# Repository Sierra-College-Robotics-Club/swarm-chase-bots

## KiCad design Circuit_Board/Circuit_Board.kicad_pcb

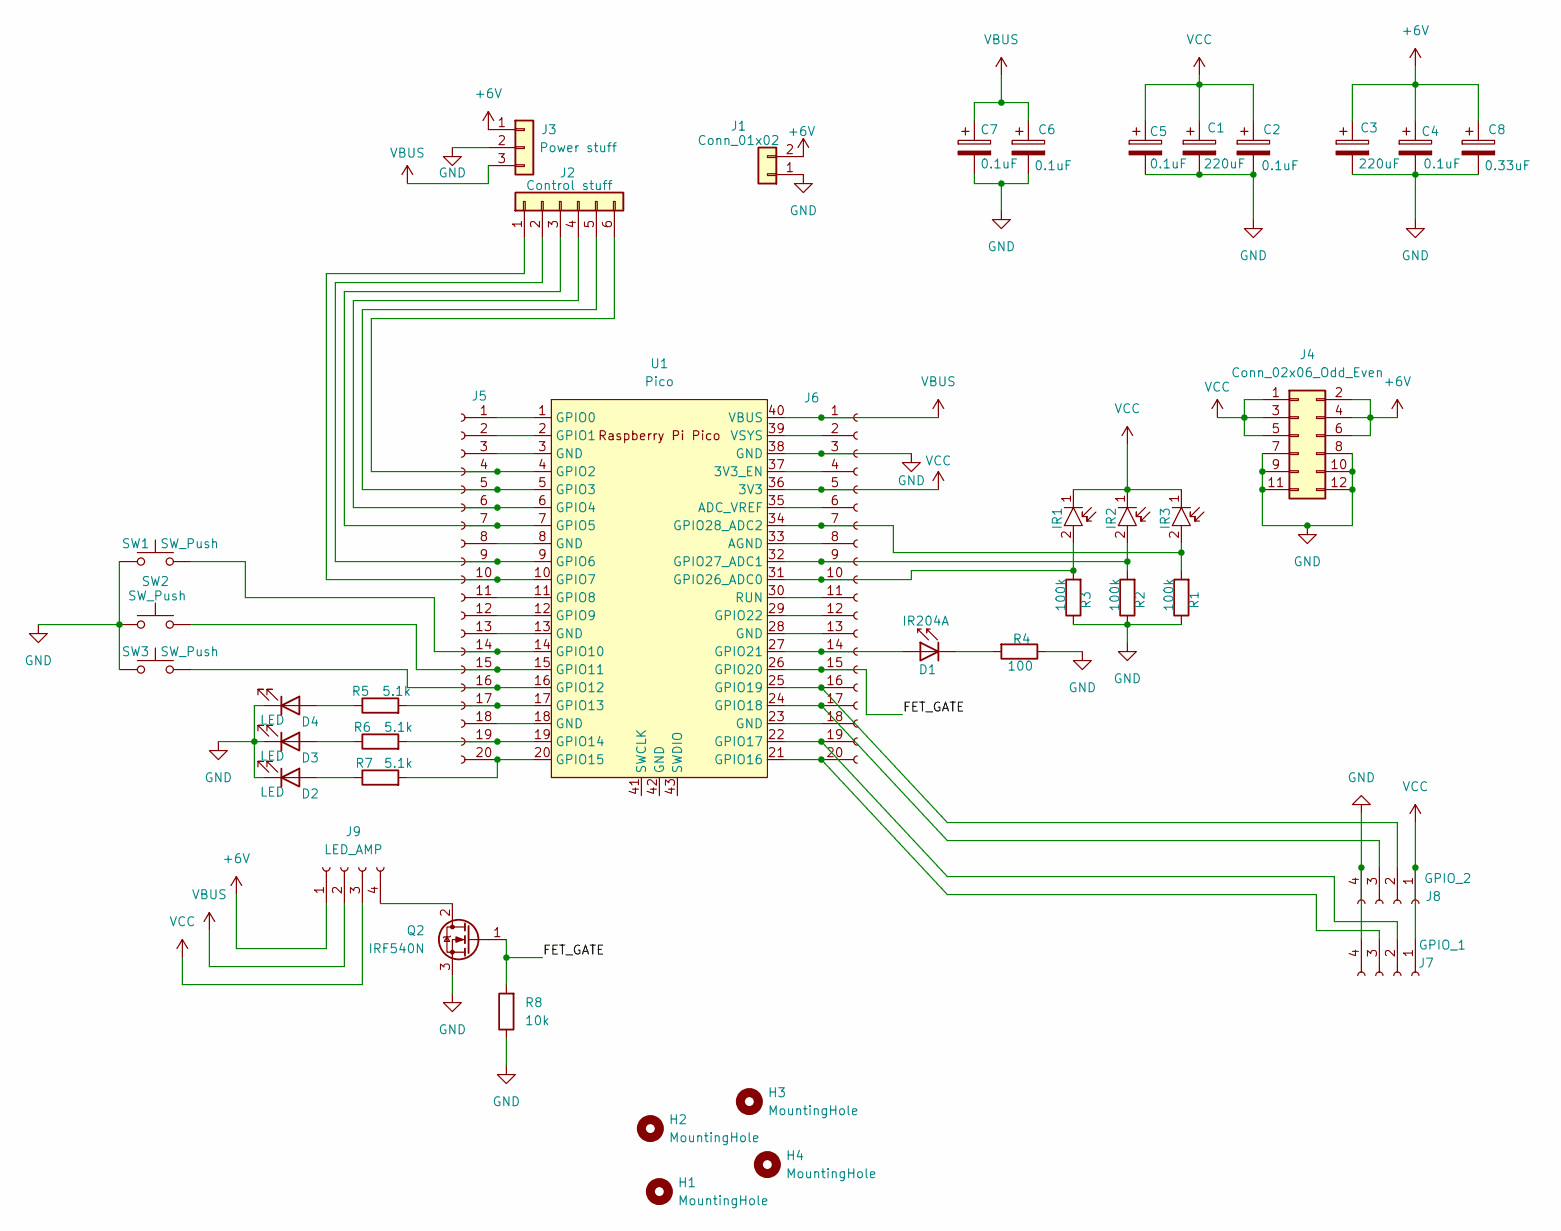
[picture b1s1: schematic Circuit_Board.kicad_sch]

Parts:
C1, C3: 220uF; CP_Radial_D10.0mm_P5.00mm
C2, C4, C5, C6, C7: 0.1uF; C_0805_2012Metric_Pad1.18x1.45mm_HandSolder
C8: 0.33uF; C_0805_2012Metric_Pad1.18x1.45mm_HandSolder
D1: IR204A; LED_D3.0mm_IRBlack
D2, D3, D4: LED; LED_0603_1608Metric_Pad1.05x0.95mm_HandSolder
H1, H2, H3, H4: MountingHole; MountingHole_3.2mm_M3
IR1, IR2, IR3: LED_D3.0mm
J1: Conn_01x02; AMASS_XT60-M_1x02_P7.20mm_Vertical
J2: Control stuff; JST_XH_B6B-XH-A_1x06_P2.50mm_Vertical
J3: Power stuff; JST_XH_B3B-XH-A_1x03_P2.50mm_Vertical
J4: Conn_02x06_Odd_Even; JST_PHD_B12B-PHDSS_2x06_P2.00mm_Vertical
J5, J6: Conn_01x20_Socket; PinSocket_1x20_P2.54mm_Vertical
J7: GPIO_1; JST_XH_B4B-XH-A_1x04_P2.50mm_Vertical
J8: GPIO_2; JST_XH_B4B-XH-A_1x04_P2.50mm_Vertical
J9: LED_AMP; JST_XH_B4B-XH-A_1x04_P2.50mm_Vertical
Q2: IRF540N; TO-220-3_Vertical
R1, R2, R3: 100k; R_0603_1608Metric_Pad0.98x0.95mm_HandSolder
R4: 100; R_0603_1608Metric_Pad0.98x0.95mm_HandSolder
R5, R6, R7: 5.1k; R_0603_1608Metric_Pad0.98x0.95mm_HandSolder
R8: 10k; R_0603_1608Metric_Pad0.98x0.95mm_HandSolder
SW1, SW2, SW3: SW_Push; SW_Push_1P1T_NO_E-Switch_TL3301NxxxxxG
U1: Pico; RPi_Pico_SMD_TH

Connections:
+6V: C3.1, C4.1, C8.1, J1.2, J3.1, J4.2, J4.4, J4.6, J9.1
/FET_GATE: J6.15, Q2.1 (G), R8.2, U1.26 (GPIO20)
GND: C1.2, C2.2, C3.2, C4.2, C5.2, C6.2, C7.2, C8.2, D2.1 (K), D3.1 (K), D4.1 (K), J1.1, J3.2, J4.7, J4.8, J4.9, J4.10, J4.11, J4.12, J6.3, J7.4, J8.4, Q2.3 (S), R1.1, R2.1, R3.1, R4.1, R8.1, SW1.1, SW2.1, SW3.1, U1.38 (GND)
unnamed: D1.2 (A), J6.14, U1.27 (GPIO21)
unnamed: D1.1 (K), R4.2
unnamed: D2.2 (A), R7.1
unnamed: D3.2 (A), R6.1
unnamed: D4.2 (A), R5.1
unnamed: J2.1, J5.10, U1.10 (GPIO7)
unnamed: J2.2, J5.9, U1.9 (GPIO6)
unnamed: J2.3, J5.7, U1.7 (GPIO5)
unnamed: J2.4, J5.6, U1.6 (GPIO4)
unnamed: J2.5, J5.5, U1.5 (GPIO3)
unnamed: J2.6, J5.4, U1.4 (GPIO2)
unnamed: J5.1, U1.1 (GPIO0)
unnamed: J5.2, U1.2 (GPIO1)
unnamed: J5.3, U1.3 (GND)
unnamed: J5.8, U1.8 (GND)
unnamed: J5.11, U1.11 (GPIO8)
unnamed: J5.12, U1.12 (GPIO9)
unnamed: J5.13, U1.13 (GND)
unnamed: J5.14, SW1.2, U1.14 (GPIO10)
unnamed: J5.15, SW2.2, U1.15 (GPIO11)
unnamed: J5.16, SW3.2, U1.16 (GPIO12)
unnamed: J5.17, R5.2, U1.17 (GPIO13)
unnamed: J5.18, U1.18 (GND)
unnamed: J5.19, R6.2, U1.19 (GPIO14)
unnamed: J5.20, R7.2, U1.20 (GPIO15)
unnamed: J6.2, U1.39 (VSYS)
unnamed: J6.4, U1.37 (3V3_EN)
unnamed: J6.6, U1.35 (ADC_VREF)
unnamed: IR3.2, J6.7, R1.2, U1.34 (GPIO28_ADC2)
unnamed: J6.8, U1.33 (AGND)
unnamed: IR2.2, J6.9, R2.2, U1.32 (GPIO27_ADC1)
unnamed: IR1.2, J6.10, R3.2, U1.31 (GPIO26_ADC0)
unnamed: J6.11, U1.30 (RUN)
unnamed: J6.12, U1.29 (GPIO22)
unnamed: J6.13, U1.28 (GND)
unnamed: J6.16, J8.2, U1.25 (GPIO19)
unnamed: J6.17, J8.3, U1.24 (GPIO18)
unnamed: J6.18, U1.23 (GND)
unnamed: J6.19, J7.2, U1.22 (GPIO17)
unnamed: J6.20, J7.3, U1.21 (GPIO16)
unnamed: J9.4, Q2.2 (D)
VBUS: C6.1, C7.1, J3.3, J6.1, J9.2, U1.40 (VBUS)
VCC: C1.1, C2.1, C5.1, IR1.1, IR2.1, IR3.1, J4.1, J4.3, J4.5, J6.5, J7.1, J8.1, J9.3, U1.36 (3V3)

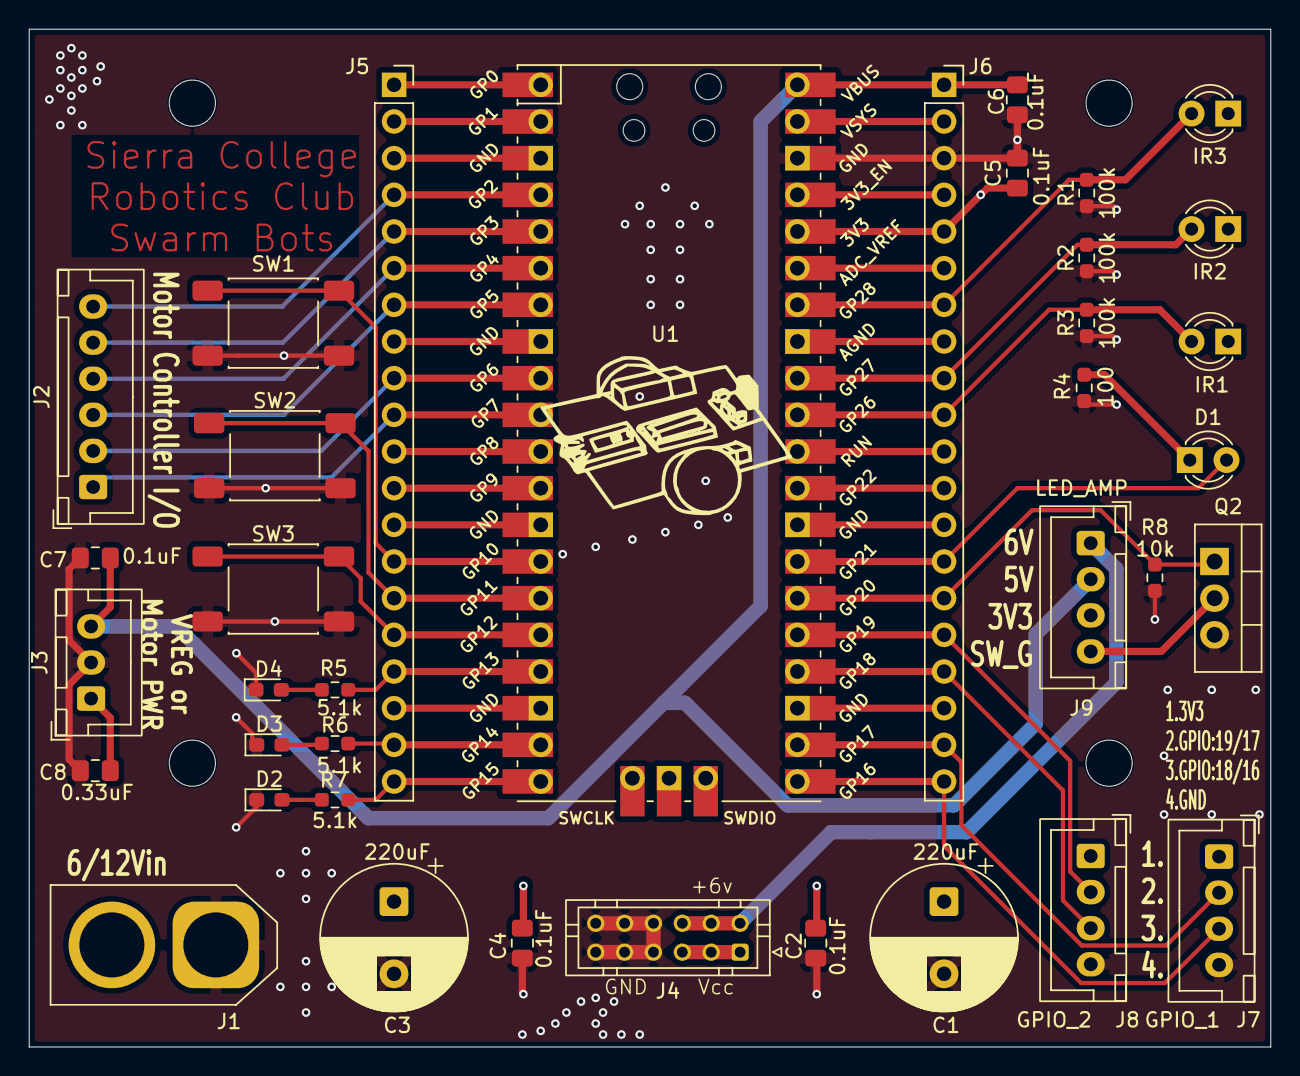
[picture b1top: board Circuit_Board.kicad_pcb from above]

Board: 4 copper layers, 86.0 x 70.5 mm, 41 parts (0 on the bottom side), 46 nets.

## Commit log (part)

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2026-03-10 Added test files for ir and motors
2026-03-10 Add main program file to move to a ir emitter
2026-03-14 Added Kicad schematic and libary files + .gitignore
2026-03-25 Added Kicad pcb and asigned footprints
2026-03-25 removed dups
2026-03-26 Started work on pcb lay and add input pins vars to main
2026-03-30 Fix footprint error and 'finished' tras routing
2026-03-31 Added turning capabilities to main.py
2026-04-07 Refined ir reading code to one fuction
2026-04-07 Changed board design
2026-04-07 v1.0 of board excluding the mounting holes
2026-04-10 Added mounting hole to PCB
2026-04-11 finalized pcb layout
2026-04-19 Made final changes to schmatic and PCB
2026-04-28 PCB Rev 1.1: Resistor value and silkscreen corrections
2026-04-28 Add BOT_NUM selector for distinct wiring adjustments
2026-05-04 update PCB with proper silkscreen value for IR LED
2026-05-06 Updated component values
2026-05-19 added support for PCB configuration of the bot
2026-05-21 Added 3d modal folder + 3d modal and updated ir emitter code
2026-05-27 updated 3D modal for robot
2026-05-27 Added smoothing code to minimze false pos WIP
2026-06-01 Updated mk1 3D modal added missing slit for cables and standardized panal 1 wall thickness
2026-06-01 fixed over turning issue in smoothing code
2026-06-10 Added transmiter button toggle to turn on IR
2026-06-16 Added new face plate to modal and add auto turning on a timer to main
2026-06-16 changed file name
2026-06-16 add LED diffuser printed with transparent PETG
2026-06-16 fix iusse with turning while stoped
2026-06-16 added light to indicate that the ir is on
2026-06-24 Add 5+ receiver front panel model, update todo note on kicad file
2026-06-24 adjusted detection thresholds, made it so you can turn off 'cower' mode, and add toggle button code
2026-06-25 add prototype of leader bot 3d modal and removable back panal
